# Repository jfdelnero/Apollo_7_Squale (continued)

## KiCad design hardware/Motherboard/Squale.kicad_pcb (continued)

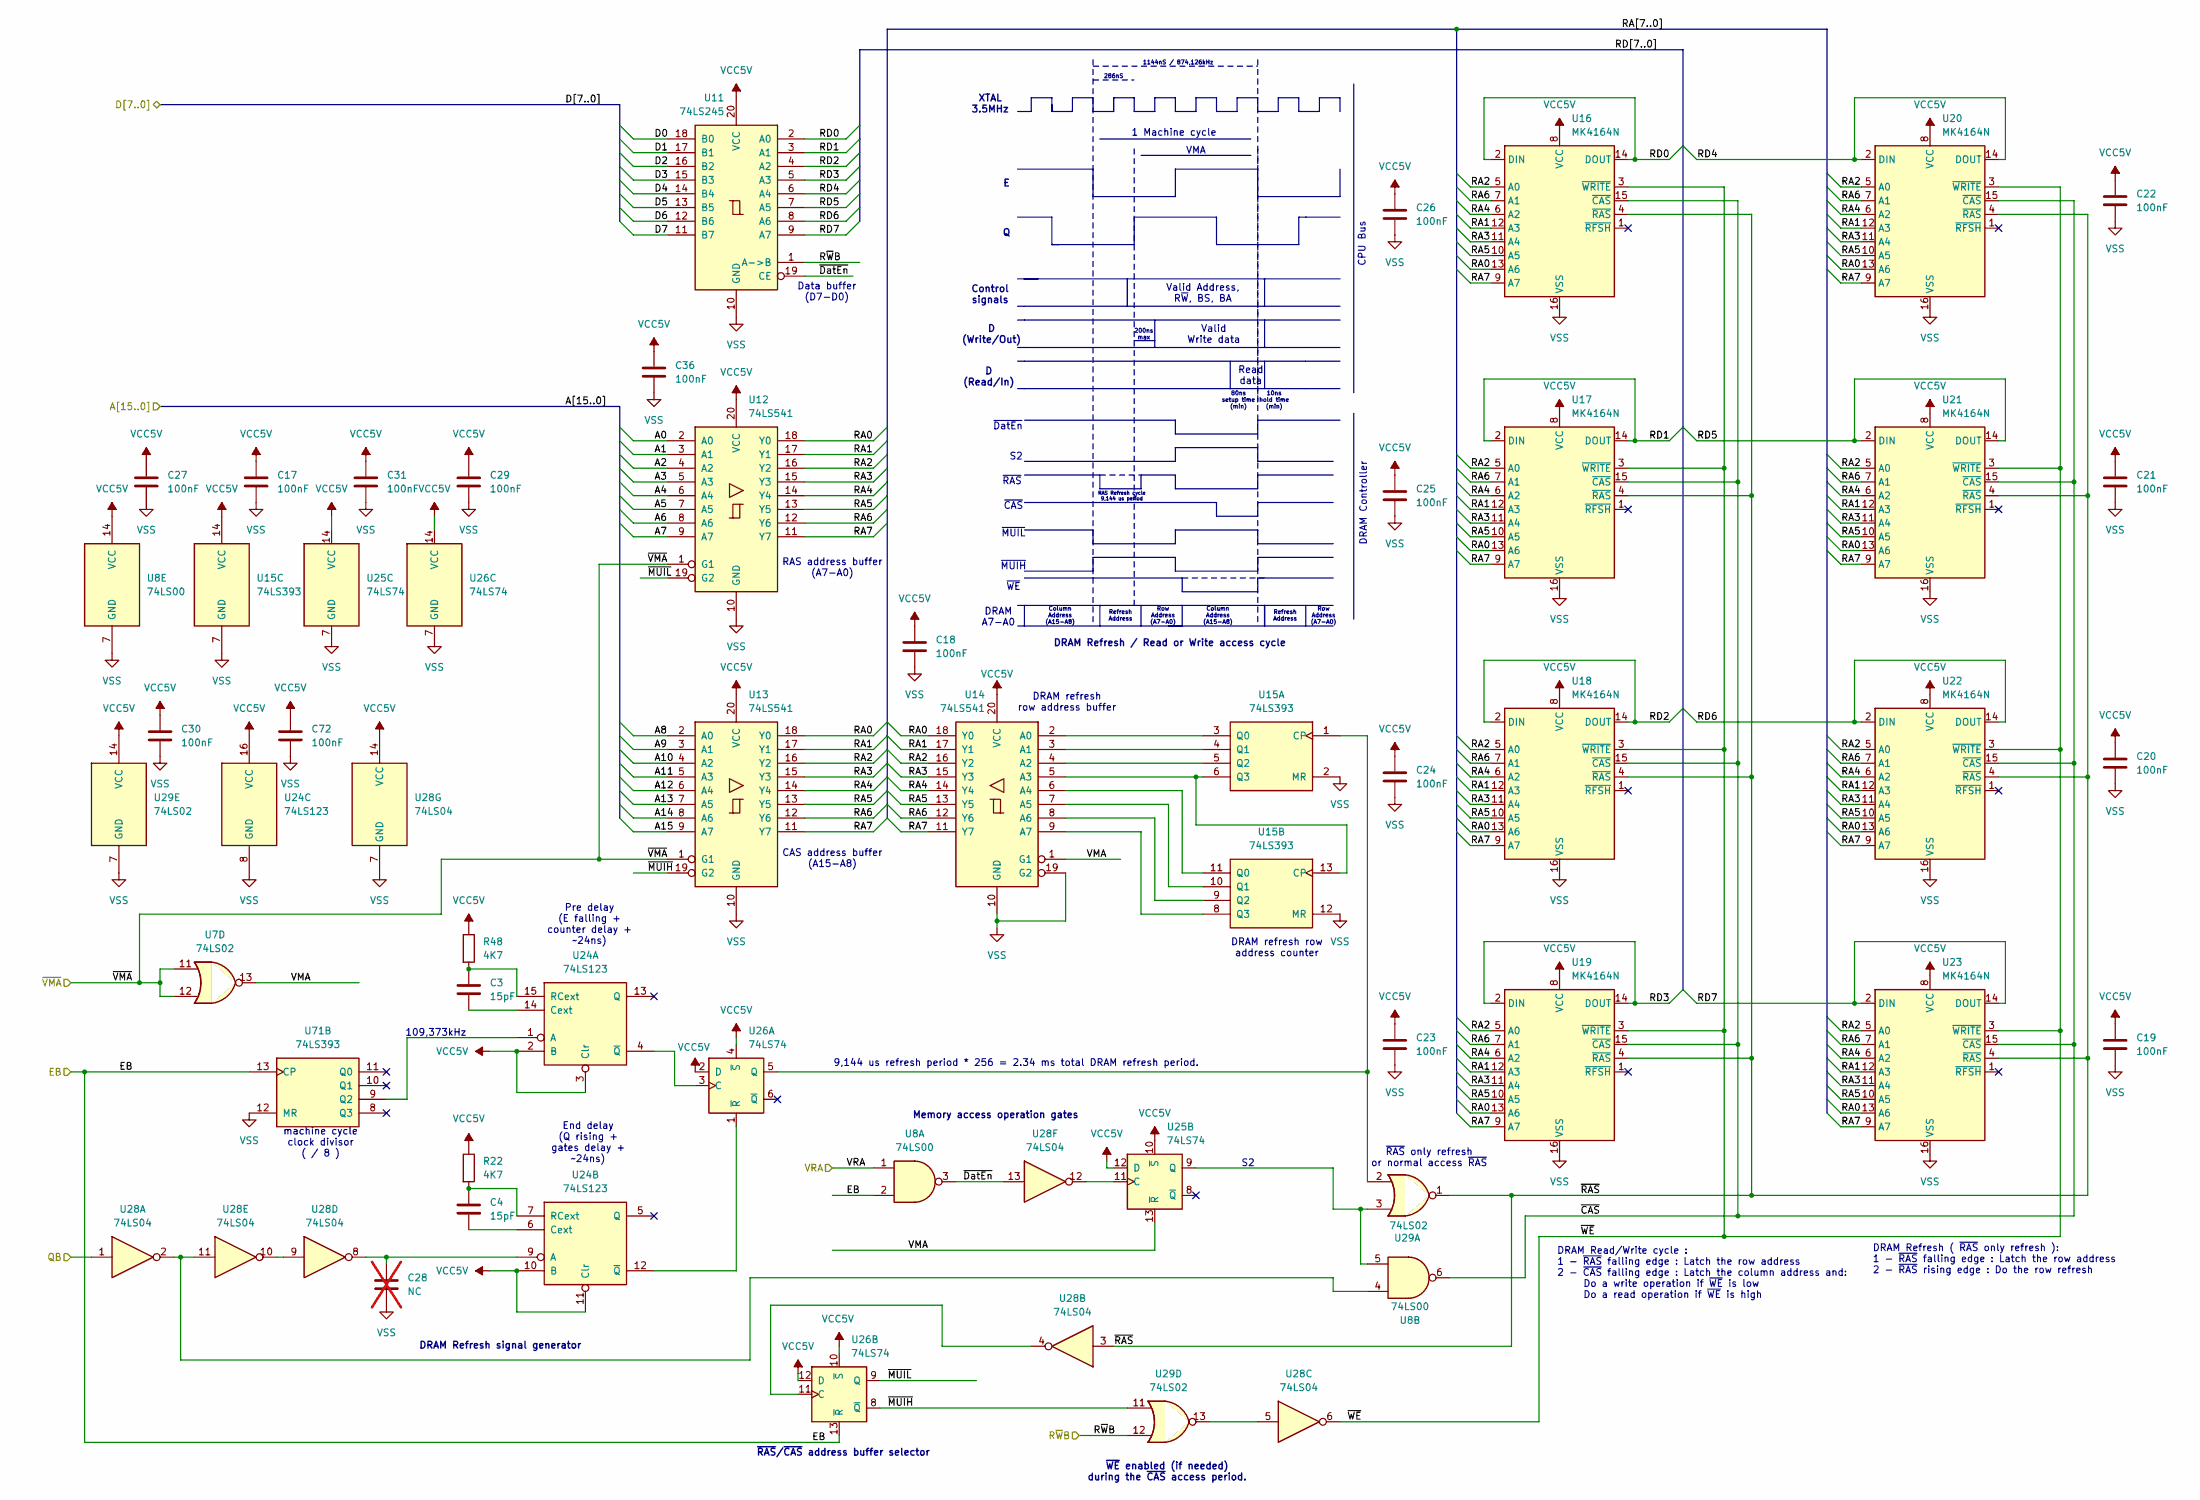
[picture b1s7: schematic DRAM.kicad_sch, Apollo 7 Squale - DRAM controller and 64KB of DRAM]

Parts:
C3, C4: 15pF; C_Disc_D3.0mm_W1.6mm_P2.50mm
C17, C18, C19, C20, C21, C22, C23, C24, C25, C26, C27, C29, C30, C31, C36, C72: 100nF; C_Disc_D9.0mm_W2.5mm_P5.00mm
C28: NC; C_Disc_D9.0mm_W2.5mm_P5.00mm; not fitted
R22, R48: 4K7; R_Axial_DIN0309_L9.0mm_D3.2mm_P12.70mm_Horizontal
U7, U29: 74LS02; DIP-14_W7.62mm_Socket
U8: 74LS00; DIP-14_W7.62mm_Socket
U11: 74LS245; DIP-20_W7.62mm_Socket
U12, U13, U14: 74LS541; DIP-20_W7.62mm_Socket
U15, U71: 74LS393; DIP-14_W7.62mm_Socket
U16, U17, U18, U19, U20, U21, U22, U23: MK4164N; DIP-16_W7.62mm_Socket
U24: 74LS123; DIP-16_W7.62mm_Socket
U25, U26: 74LS74; DIP-14_W7.62mm_Socket
U28: 74LS04; DIP-14_W7.62mm_Socket

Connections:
/A0: U12.2 (A0); also elsewhere on the board
/A1: U12.3 (A1); also elsewhere on the board
/A2: U12.4 (A2); also elsewhere on the board
/A3: U12.5 (A3); also elsewhere on the board
/A4: U12.6 (A4); also elsewhere on the board
/A5: U12.7 (A5); also elsewhere on the board
/A6: U12.8 (A6); also elsewhere on the board
/A7: U12.9 (A7); also elsewhere on the board
/A8: U13.2 (A0); also elsewhere on the board
/A9: U13.3 (A1); also elsewhere on the board
/A10: U13.4 (A2); also elsewhere on the board
/A11: U13.5 (A3); also elsewhere on the board
/A12: U13.6 (A4); also elsewhere on the board
/A13: U13.7 (A5); also elsewhere on the board
/A14: U13.8 (A6); also elsewhere on the board
/A15: U13.9 (A7); also elsewhere on the board
/CPU/EB: U8.2, U26.13 (~R), U71.13 (CP); also elsewhere on the board
/CPU/QB: U28.1; also elsewhere on the board
/CPU/R~WB: U11.1 (A->B), U29.12; also elsewhere on the board
/CPU/VRA: U8.1; also elsewhere on the board
/CPU/~VMA: U7.11, U7.12, U12.1 (G1), U13.1 (G1); also elsewhere on the board
/D0: U11.18 (B0); also elsewhere on the board
/D1: U11.17 (B1); also elsewhere on the board
/D2: U11.16 (B2); also elsewhere on the board
/D3: U11.15 (B3); also elsewhere on the board
/D4: U11.14 (B4); also elsewhere on the board
/D5: U11.13 (B5); also elsewhere on the board
/D6: U11.12 (B6); also elsewhere on the board
/D7: U11.11 (B7); also elsewhere on the board
/DRAM/RA0: U12.18 (Y0), U13.18 (Y0), U14.18 (Y0), U16.13 (A6), U17.13 (A6), U18.13 (A6), U19.13 (A6), U20.13 (A6), U21.13 (A6), U22.13 (A6), U23.13 (A6)
/DRAM/RA1: U12.17 (Y1), U13.17 (Y1), U14.17 (Y1), U16.12 (A3), U17.12 (A3), U18.12 (A3), U19.12 (A3), U20.12 (A3), U21.12 (A3), U22.12 (A3), U23.12 (A3)
/DRAM/RA2: U12.16 (Y2), U13.16 (Y2), U14.16 (Y2), U16.5 (A0), U17.5 (A0), U18.5 (A0), U19.5 (A0), U20.5 (A0), U21.5 (A0), U22.5 (A0), U23.5 (A0)
/DRAM/RA3: U12.15 (Y3), U13.15 (Y3), U14.15 (Y3), U16.11 (A4), U17.11 (A4), U18.11 (A4), U19.11 (A4), U20.11 (A4), U21.11 (A4), U22.11 (A4), U23.11 (A4)
/DRAM/RA4: U12.14 (Y4), U13.14 (Y4), U14.14 (Y4), U16.6 (A2), U17.6 (A2), U18.6 (A2), U19.6 (A2), U20.6 (A2), U21.6 (A2), U22.6 (A2), U23.6 (A2)
/DRAM/RA5: U12.13 (Y5), U13.13 (Y5), U14.13 (Y5), U16.10 (A5), U17.10 (A5), U18.10 (A5), U19.10 (A5), U20.10 (A5), U21.10 (A5), U22.10 (A5), U23.10 (A5)
/DRAM/RA6: U12.12 (Y6), U13.12 (Y6), U14.12 (Y6), U16.7 (A1), U17.7 (A1), U18.7 (A1), U19.7 (A1), U20.7 (A1), U21.7 (A1), U22.7 (A1), U23.7 (A1)
/DRAM/RA7: U12.11 (Y7), U13.11 (Y7), U14.11 (Y7), U16.9 (A7), U17.9 (A7), U18.9 (A7), U19.9 (A7), U20.9 (A7), U21.9 (A7), U22.9 (A7), U23.9 (A7)
/DRAM/RD0: U11.2 (A0), U16.2 (DIN), U16.14 (DOUT)
/DRAM/RD1: U11.3 (A1), U17.2 (DIN), U17.14 (DOUT)
/DRAM/RD2: U11.4 (A2), U18.2 (DIN), U18.14 (DOUT)
/DRAM/RD3: U11.5 (A3), U19.2 (DIN), U19.14 (DOUT)
/DRAM/RD4: U11.6 (A4), U20.2 (DIN), U20.14 (DOUT)
/DRAM/RD5: U11.7 (A5), U21.2 (DIN), U21.14 (DOUT)
/DRAM/RD6: U11.8 (A6), U22.2 (DIN), U22.14 (DOUT)
/DRAM/RD7: U11.9 (A7), U23.2 (DIN), U23.14 (DOUT)
/DRAM/VMA: U7.13, U14.1 (G1), U25.13 (~R)
/DRAM/~CAS: U8.6, U16.15 (~CAS), U17.15 (~CAS), U18.15 (~CAS), U19.15 (~CAS), U20.15 (~CAS), U21.15 (~CAS), U22.15 (~CAS), U23.15 (~CAS)
/DRAM/~DatEn: U8.3, U11.19 (CE), U28.13
/DRAM/~MUIH: U13.19 (G2), U26.8 (~Q), U29.11
/DRAM/~MUIL: U12.19 (G2), U26.9 (Q)
/DRAM/~RAS: U16.4 (~RAS), U17.4 (~RAS), U18.4 (~RAS), U19.4 (~RAS), U20.4 (~RAS), U21.4 (~RAS), U22.4 (~RAS), U23.4 (~RAS), U28.3, U29.1
/DRAM/~WE: U16.3 (~WRITE), U17.3 (~WRITE), U18.3 (~WRITE), U19.3 (~WRITE), U20.3 (~WRITE), U21.3 (~WRITE), U22.3 (~WRITE), U23.3 (~WRITE), U28.6
unnamed: U14.2 (A0), U15.3 (Q0)
unnamed: U14.3 (A1), U15.4 (Q1)
unnamed: U14.4 (A2), U15.5 (Q2)
unnamed: U14.5 (A3), U15.6 (Q3), U15.13 (CP)
unnamed: U14.6 (A4), U15.11 (Q0)
unnamed: U14.7 (A5), U15.10 (Q1)
unnamed: U14.8 (A6), U15.9 (Q2)
unnamed: U14.9 (A7), U15.8 (Q3)
unnamed: U15.1 (CP), U26.5 (Q), U29.2
unnamed: U24.1 (A), U71.9 (Q2)
unnamed: C3.2, U24.14 (Cext)
unnamed: C3.1, R48.2, U24.15 (RCext)
unnamed: U24.4 (~Q), U26.3 (C)
unnamed: C28.1, U24.9 (A), U28.8
unnamed: C4.2, U24.6 (Cext)
unnamed: C4.1, R22.2, U24.7 (RCext)
unnamed: U24.12 (~Q), U26.1 (~R)
unnamed: U25.11 (C), U28.12
unnamed: U8.5, U25.9 (Q), U29.3
unnamed: U26.11 (C), U28.4
unnamed: U28.5, U29.13
unnamed: U28.9, U28.10
unnamed: U8.4, U28.2, U28.11
VCC5V: C17.1, C18.1, C19.1, C20.1, C21.1, C22.1, C23.1, C24.1, C25.1, C26.1, C27.1, C29.1, C30.1, C31.1, C36.1, C72.1, R22.1, R48.1, U8.14 (VCC), U11.20 (VCC), U12.20 (VCC), U13.20 (VCC), U14.20 (VCC), U15.14 (VCC), U16.8 (VCC), U17.8 (VCC), U18.8 (VCC), U19.8 (VCC), U20.8 (VCC), U21.8 (VCC), U22.8 (VCC), U23.8 (VCC), U24.2 (B), U24.3 (Clr), U24.10 (B), U24.11 (Clr), U24.16 (VCC), U25.10 (~S), U25.12 (D), U25.14 (VCC), U26.2 (D), U26.4 (~S), U26.10 (~S), U26.12 (D), U26.14 (VCC), U28.14 (VCC), U29.14 (VCC); also elsewhere on the board
VSS: C17.2, C18.2, C19.2, C20.2, C21.2, C22.2, C23.2, C24.2, C25.2, C26.2, C27.2, C28.2, C29.2, C30.2, C31.2, C36.2, C72.2, U8.7 (GND), U11.10 (GND), U12.10 (GND), U13.10 (GND), U14.10 (GND), U14.19 (G2), U15.2 (MR), U15.7 (GND), U15.12 (MR), U16.16 (VSS), U17.16 (VSS), U18.16 (VSS), U19.16 (VSS), U20.16 (VSS), U21.16 (VSS), U22.16 (VSS), U23.16 (VSS), U24.8 (GND), U25.7 (GND), U26.7 (GND), U28.7 (GND), U29.7 (GND), U71.12 (MR); also elsewhere on the board

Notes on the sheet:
CPU Bus
~{WE}
Control signals
Read data
DRAM refresh row address buffer
RAS address buffer (A7-A0)
Memory access operation gates
~{RAS} only refresh or normal access ~{RAS}
Column Address (A15-A8)
Valid Write data
109,373kHz
~{RAS}
CAS address buffer (A15-A8)
XTAL 3.5MHz
Row Address (A7-A0)
286nS
machine cycle clock divisor ( / 8 )
Valid Address, R~{W}, BS, BA
DRAM Controller
DRAM refresh row address counter
D (Read/In)
D (Write/Out)
~{WE} enabled (if needed) during the ~{CAS} access period.
~{MUIH}
End delay (Q rising + gates delay + ~24ns)
~{MUIL}
200ns max
~{DatEn}
DRAM A7-A0
Refresh Address
9,144 us refresh period * 256 = 2.34 ms total DRAM refresh period.
10ns hold time (min)
VMA
DRAM Refresh signal generator
DRAM Refresh ( ~{RAS} only refresh ): 1 - ~{RAS} falling edge : Latch the row address 2 - ~{RAS} rising edge : Do the row refresh
~{RAS}/~{CAS} address buffer selector
1 Machine cycle
Data buffer (D7-D0)
80ns setup time (min)
DRAM Refresh / Read or Write access cycle

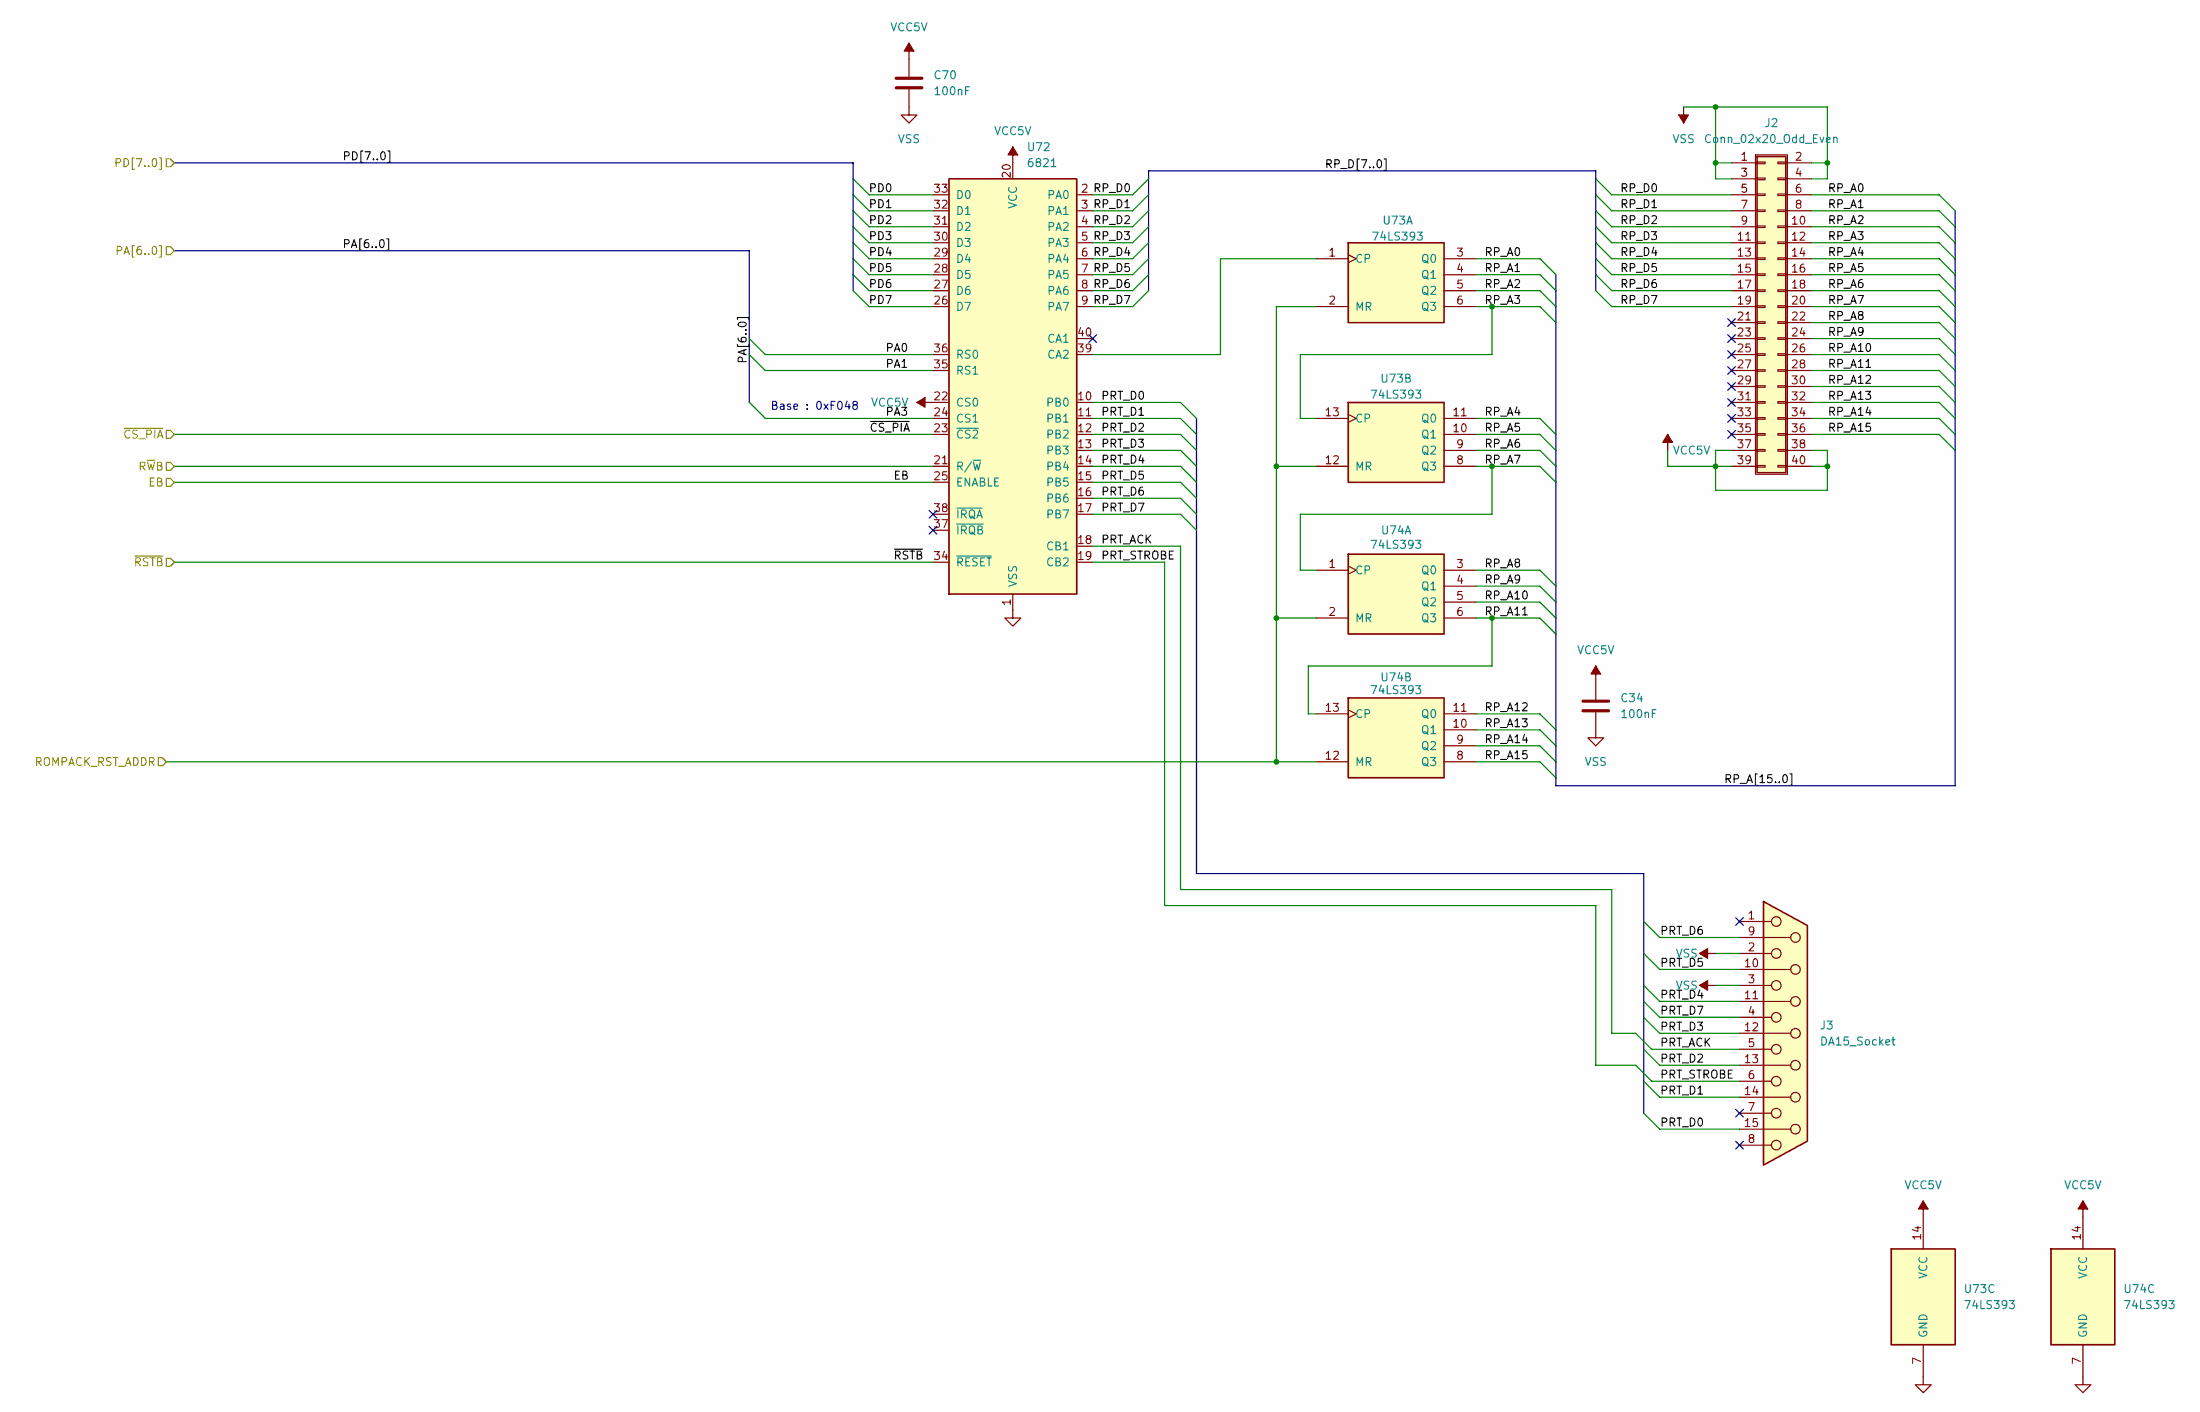
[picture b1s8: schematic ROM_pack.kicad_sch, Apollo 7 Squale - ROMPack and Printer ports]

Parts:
C34, C70: 100nF; C_Disc_D9.0mm_W2.5mm_P5.00mm
J2: Conn_02x20_Odd_Even; Ribbon_Conn
J3: DA15_Socket; DSUB-15_Pins_Horizontal_P2.77x2.84mm_EdgePinOffset9.40mm
U72: 6821; DIP-40_W15.24mm_Socket
U73, U74: 74LS393; DIP-14_W7.62mm_Socket

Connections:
/CPU/EB: U72.25 (ENABLE); also elsewhere on the board
/CPU/R~WB: U72.21 (R/~W); also elsewhere on the board
/CPU/~CS_PIA: U72.23 (~CS2); also elsewhere on the board
/Keyboard/ROMPACK_RST_ADDR: U73.2 (MR), U73.12 (MR), U74.2 (MR), U74.12 (MR); also elsewhere on the board
/Keyboard/~RSTB: U72.34 (~RESET); also elsewhere on the board
/PA0: U72.36 (RS0); also elsewhere on the board
/PA1: U72.35 (RS1); also elsewhere on the board
/PA3: U72.24 (CS1); also elsewhere on the board
/PD0: U72.33 (D0); also elsewhere on the board
/PD1: U72.32 (D1); also elsewhere on the board
/PD2: U72.31 (D2); also elsewhere on the board
/PD3: U72.30 (D3); also elsewhere on the board
/PD4: U72.29 (D4); also elsewhere on the board
/PD5: U72.28 (D5); also elsewhere on the board
/PD6: U72.27 (D6); also elsewhere on the board
/PD7: U72.26 (D7); also elsewhere on the board
/ROM_pack/PRT_ACK: J3.5, U72.18 (CB1)
/ROM_pack/PRT_D0: J3.15, U72.10 (PB0)
/ROM_pack/PRT_D1: J3.14, U72.11 (PB1)
/ROM_pack/PRT_D2: J3.13, U72.12 (PB2)
/ROM_pack/PRT_D3: J3.12, U72.13 (PB3)
/ROM_pack/PRT_D4: J3.11 (P111), U72.14 (PB4)
/ROM_pack/PRT_D5: J3.10, U72.15 (PB5)
/ROM_pack/PRT_D6: J3.9, U72.16 (PB6)
/ROM_pack/PRT_D7: J3.4, U72.17 (PB7)
/ROM_pack/PRT_STROBE: J3.6, U72.19 (CB2)
/ROM_pack/RP_A0: J2.6, U73.3 (Q0)
/ROM_pack/RP_A1: J2.8, U73.4 (Q1)
/ROM_pack/RP_A2: J2.10, U73.5 (Q2)
/ROM_pack/RP_A3: J2.12, U73.6 (Q3), U73.13 (CP)
/ROM_pack/RP_A4: J2.14, U73.11 (Q0)
/ROM_pack/RP_A5: J2.16, U73.10 (Q1)
/ROM_pack/RP_A6: J2.18, U73.9 (Q2)
/ROM_pack/RP_A7: J2.20, U73.8 (Q3), U74.1 (CP)
/ROM_pack/RP_A8: J2.22, U74.3 (Q0)
/ROM_pack/RP_A9: J2.24, U74.4 (Q1)
/ROM_pack/RP_A10: J2.26, U74.5 (Q2)
/ROM_pack/RP_A11: J2.28, U74.6 (Q3), U74.13 (CP)
/ROM_pack/RP_A12: J2.30, U74.11 (Q0)
/ROM_pack/RP_A13: J2.32, U74.10 (Q1)
/ROM_pack/RP_A14: J2.34, U74.9 (Q2)
/ROM_pack/RP_A15: J2.36, U74.8 (Q3)
/ROM_pack/RP_D0: J2.5, U72.2 (PA0)
/ROM_pack/RP_D1: J2.7, U72.3 (PA1)
/ROM_pack/RP_D2: J2.9, U72.4 (PA2)
/ROM_pack/RP_D3: J2.11, U72.5 (PA3)
/ROM_pack/RP_D4: J2.13, U72.6 (PA4)
/ROM_pack/RP_D5: J2.15, U72.7 (PA5)
/ROM_pack/RP_D6: J2.17, U72.8 (PA6)
/ROM_pack/RP_D7: J2.19, U72.9 (PA7)
unnamed: U72.39 (CA2), U73.1 (CP)
VCC5V: C34.1, C70.1, J2.37, J2.38, J2.39, J2.40, U72.20 (VCC), U72.22 (CS0), U73.14 (VCC), U74.14 (VCC); also elsewhere on the board
VSS: C34.2, C70.2, J2.1, J2.2, J2.3, J2.4, J3.2, J3.3, U72.1 (VSS), U73.7 (GND), U74.7 (GND); also elsewhere on the board

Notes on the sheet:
Base : 0xF048

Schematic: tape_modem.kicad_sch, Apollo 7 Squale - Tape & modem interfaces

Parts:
C5: 22pF; C_Disc_D3.0mm_W1.6mm_P2.50mm
C6: 10pF; C_Disc_D3.0mm_W1.6mm_P2.50mm
C7, C8: 10uF 50V; C_Radial_D6.3mm_H5.0mm_P2.50mm
C9, C11, C12, C13, C39, C40, C41: 100nF; C_Disc_D9.0mm_W2.5mm_P5.00mm
C10: 68pF; C_Disc_D6.0mm_W2.5mm_P5.00mm
D1, D2: 1N4148; D_DO-35_SOD27_P12.70mm_Horizontal
J5: DIN-5_180degree; DIN5-RA-PTH
J6: DE9_Socket; DSUB-9_Socket_Horizontal_P2.77x2.54mm_EdgePinOffset9.40mm
P1: VR10K; Potentiometer_Piher_PT-10-H01_Horizontal
R23, R26, R29, R30, R33, R34, R35, R37: 10K; R_Axial_DIN0309_L9.0mm_D3.2mm_P12.70mm_Horizontal
R24: 330K; R_Axial_DIN0309_L9.0mm_D3.2mm_P12.70mm_Horizontal
R25, R27, R36: 47K; R_Axial_DIN0309_L9.0mm_D3.2mm_P12.70mm_Horizontal
R28: 33K3; R_Axial_DIN0309_L9.0mm_D3.2mm_P12.70mm_Horizontal
R31, R47: 470R; R_Axial_DIN0309_L9.0mm_D3.2mm_P12.70mm_Horizontal
R32: 22K; R_Axial_DIN0309_L9.0mm_D3.2mm_P12.70mm_Horizontal
U67: TL084; DIP-14_W7.62mm_Socket
U68: EFB7510; DIP-18_W7.62mm_Socket
U69: MC6850; DIP-24_W15.24mm_Socket
U70: 74LS02; DIP-14_W7.62mm_Socket
U71: 74LS393; DIP-14_W7.62mm_Socket
Y2: 3.579MHz; Crystal_HC18-U_Vertical

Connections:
/CPU/EB: U69.14 (E); also elsewhere on the board
/CPU/R~WB: U69.13 (R/~W); also elsewhere on the board
/CPU/~CS_ACIA: U69.9 (CS2); also elsewhere on the board
/PA0: U69.11 (RS); also elsewhere on the board
/PD0: U69.22 (D0); also elsewhere on the board
/PD1: U69.21 (D1); also elsewhere on the board
/PD2: U69.20 (D2); also elsewhere on the board
/PD3: U69.19 (D3); also elsewhere on the board
/PD4: U69.18 (D4); also elsewhere on the board
/PD5: U69.17 (D5); also elsewhere on the board
/PD6: U69.16 (D6); also elsewhere on the board
/PD7: U69.15 (D7); also elsewhere on the board
/Sound/MODEM_RING: J6.2; also elsewhere on the board
/Tape-Modem/IN_1: J5.3, R35.1, R36.2, R37.2
/Tape-Modem/IN_2: J5.5, R35.2
/Tape-Modem/MDM_CLK_19K2: U68.16 (RxCLK), U69.3 (Rx_CLK), U70.3, U71.1 (CP)
/Tape-Modem/MDM_CLK_TX: U69.4 (Tx_CLK), U70.4
/Tape-Modem/OUT_1V_LEVEL: J5.4, R33.2, R34.1
/Tape-Modem/OUT_50mV_LEVEL: J5.1, R34.2, R47.2
/Tape-Modem/SYS_MDM_LINE: J6.1; also elsewhere on the board
/Tape-Modem/SYS_MDM_MC_~BC: U68.18 (MC/~BC), U70.8, U70.11, U70.12; also elsewhere on the board
unnamed: C9.1, R23.2
unnamed: C10.1, C11.2, R24.1, U67.8
unnamed: C12.1, R26.2
unnamed: C13.1, R32.1
unnamed: C11.1, C12.2, D1.2 (A), D2.1 (K), R25.1
unnamed: C9.2, C10.2, D1.1 (K), D2.2 (A), R24.2, U67.9 (-)
unnamed: R28.1, R29.2, R31.2, R33.1, U67.1
unnamed: R28.2, R32.2, U67.2 (-)
unnamed: J6.4, R31.1, U67.5 (+)
unnamed: R29.1, R30.2, R36.1, U67.6 (-)
unnamed: R26.1, R27.2, U67.13 (-)
unnamed: C13.2, U68.4 (ATO)
unnamed: R30.1, U67.7, U68.7 (RAI)
unnamed: R27.1, U67.14, U68.13 (RDI)
unnamed: R23.1, U68.5 (RFO)
unnamed: P1.2, U68.9 (RSA)
unnamed: U68.11 (RXD), U69.2 (Rx_Data)
unnamed: U68.17 (TXD), U69.6 (Tx_Data)
unnamed: P1.3, U68.10 (VREF)
unnamed: C5.1, U68.15 (XTAL_IN), Y2.1
unnamed: C6.2, U68.14 (XTAL_OUT), Y2.2
unnamed: U68.12 (~DCD), U69.23 (~DCD)
unnamed: U68.2 (~RTS), U69.5 (~RTS)
unnamed: U70.1, U70.6
unnamed: U70.5, U70.10
unnamed: U70.2, U70.13
unnamed: U70.9, U71.6 (Q3)
VCC5V: C8.1, C39.1, C40.1, J6.3, U67.4 (V+), U68.1 (V+), U69.8 (CS0), U69.10 (CS1), U69.12 (VCC), U70.14 (VCC), U71.14 (VCC); also elsewhere on the board
VEE5V: C7.1, C41.2, U67.11 (V-), U68.6 (V-); also elsewhere on the board
VSS: C5.2, C6.1, C7.2, C8.2, C39.2, C40.2, C41.1, J5.2, J6.5, J6.8, P1.1, R25.2, R37.1, R47.1, U67.3 (+), U67.10 (+), U67.12 (+), U68.3 (GNDD), U68.8 (GNDA), U69.1 (VSS), U69.24 (~CTS), U70.7 (GND), U71.2 (MR), U71.7 (GND); also elsewhere on the board

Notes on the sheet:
+/- 1.20V
Typical output level : +/- 1.56V
Peak limiter band pass filter
TX Clock source selector. SYS_MDM_MC_~{BC} Low : 1200 Hz (75 Baud) SYS_MDM_MC_~{BC} High : 19200 Hz (1200 Baud)
G = 47K/10K = 4,7 20 * log 4,7 = 13,44 dB
/ 22.28 -26.95 dB
High pass filter Cutoff frequency (-3 dB) : fc = 1 / ( 2 * PI * 10K * 100nF ) = 159.15 Hz
peak limiter (1V)
Peak limiter band pass filter curve
Duplexer
Low pass filter G = 330K/10K = 33 20 * log 33 = 30,37 dB Cutoff frequency (-3 dB) : fc = 1 / ( 2 * PI * 330K * 68pF ) = 7092.47 Hz
+/- 54mV
max level : +8 dBm (< 6 VPP)
(1200 Hz -> 75 Baud) (19200 Hz -> 1200 Baud)
G = 33K3/22K = * 1.514 20 * log 1.514 = +3,6 dB
+/- 2.36V
TX baudrate selection Low = 75 baud High = 1200 baud.
RxCLK divisor 19200Hz / 16 = 1200 Hz (1200 Hz -> 75 Baud)

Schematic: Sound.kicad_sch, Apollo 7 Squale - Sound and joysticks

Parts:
C14: ??; C_Disc_D9.0mm_W2.5mm_P5.00mm
C15: 10uF 50V; C_Radial_D6.3mm_H5.0mm_P2.50mm
C42: 100nF; C_Disc_D9.0mm_W2.5mm_P5.00mm
J7, J8: DE9_Pins; DSUB-9_Pins_Horizontal_P2.77x2.54mm_EdgePinOffset9.40mm
R38, R39: 1K; R_Axial_DIN0309_L9.0mm_D3.2mm_P12.70mm_Horizontal
R40: 10K; R_Axial_DIN0309_L9.0mm_D3.2mm_P12.70mm_Horizontal
U29: 74LS02; DIP-14_W7.62mm_Socket
U65: AY-3-8910A; DIP-40_W15.24mm_Socket

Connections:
/A0: U29.6; also elsewhere on the board
/CPU/R~WB: U29.8; also elsewhere on the board
/CPU/~CS_AY: U29.5, U29.9; also elsewhere on the board
/Clocks/CLK_1.75MHz: U65.22 (CLOCK); also elsewhere on the board
/Keyboard/KEYB_CTRL: U65.7 (IOB6); also elsewhere on the board
/Keyboard/KEYB_LOCK: U65.9 (IOB4); also elsewhere on the board
/Keyboard/KEYB_SHIFT: U65.8 (IOB5); also elsewhere on the board
/Keyboard/~RSTB: U65.23 (~RESET); also elsewhere on the board
/PD0: U65.37 (DA0); also elsewhere on the board
/PD1: U65.36 (DA1); also elsewhere on the board
/PD2: U65.35 (DA2); also elsewhere on the board
/PD3: U65.34 (DA3); also elsewhere on the board
/PD4: U65.33 (DA4); also elsewhere on the board
/PD5: U65.32 (DA5); also elsewhere on the board
/PD6: U65.31 (DA6); also elsewhere on the board
/PD7: U65.30 (DA7); also elsewhere on the board
/Sound/JOY1_DOWN: J7.2, U65.19 (IOA2)
/Sound/JOY1_FIRE: J7.6, U65.14 (IOA7)
/Sound/JOY1_LEFT: J7.3, U65.20 (IOA1)
/Sound/JOY1_RIGHT: J7.4, U65.21 (IOA0)
/Sound/JOY1_UP: J7.1, U65.18 (IOA3)
/Sound/JOY2_DOWN: J8.2, U65.11 (IOB2)
/Sound/JOY2_FIRE: J8.6, U65.6 (IOB7)
/Sound/JOY2_LEFT: J8.3, U65.12 (IOB1)
/Sound/JOY2_RIGHT: J8.4, U65.13 (IOB0)
/Sound/JOY2_UP: J8.1, U65.10 (IOB3)
/Sound/LIGHTPEN_SWITCH: U65.16 (IOA5); also elsewhere on the board
/Sound/MODEM_RING: U65.15 (IOA6); also elsewhere on the board
/Sound/SOUND_OUT: C14.1, R39.2, R40.1; also elsewhere on the board
unnamed: C15.2, R39.1
unnamed: C15.1, R38.1, U65.3 (A), U65.4 (B), U65.38 (C)
unnamed: U29.4, U65.29 (BC1)
unnamed: U29.10, U65.27 (BDIR)
VCC5V: C42.1, J7.7, J8.7, U65.25 (A8), U65.28 (BC2), U65.40 (VCC); also elsewhere on the board
VSS: C14.2, C42.2, J7.8, J8.8, R38.2, R40.2, U65.1 (VSS), U65.24 (~A9); also elsewhere on the board

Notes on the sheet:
Base address : 0xF060

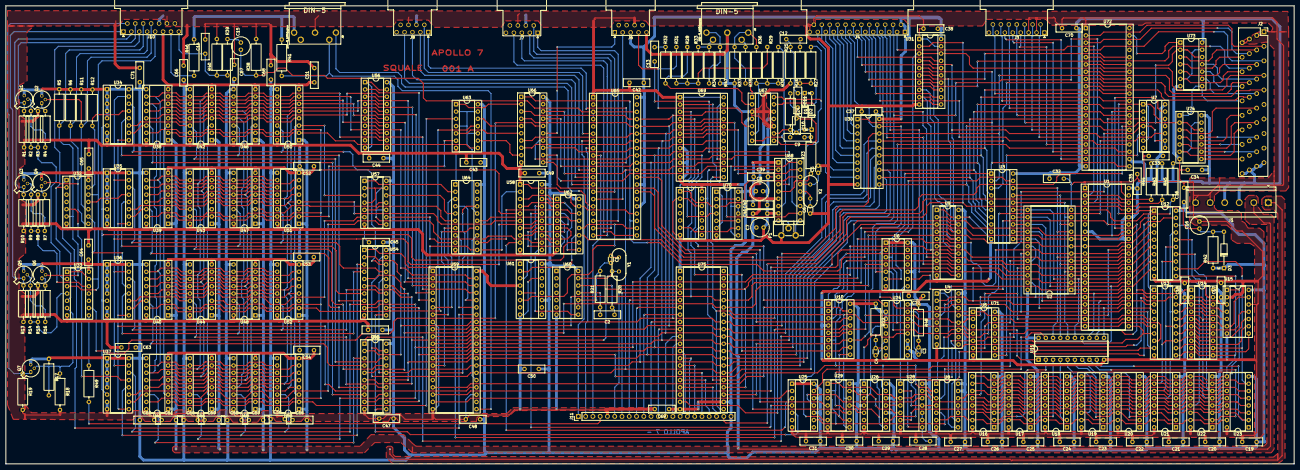
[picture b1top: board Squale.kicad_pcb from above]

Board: 2 copper layers, 450.0 x 160.0 mm, 219 parts (0 on the bottom side), 351 nets.

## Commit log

2019-10-14 Squale toolchain generation scripts.
2019-10-14 Squale Tape/Cartridge generators tools.
2019-10-14 linker script and program loader/header.
2019-10-14 gcc 4.6.3 cross compile patch.
2019-10-14 A very first/simple Squale Intro/demo.
2019-10-14 WIP : Squale 3D demo.
2019-10-15 Squale specific headers.
2019-10-17 Add more Squale HW definition.
2019-10-17 Update HW defines.
2019-10-17 Update HW defines. 3d objects change.
2019-10-19 Build tape wav file.
2019-10-19 use WR_BYTE instead of a pointer. fix some glitches on the real machine : wait the end of the last line draw.
2019-10-19 interrupt driven music player.
2019-10-20 YM player : YM data are now "packed". Bigger YM music can now be used.
2019-10-20 A "poor-man"/quick and dirty ym packer/converter. Anyway this "packed" form is now played on a the 6809 machine without the need to deflate the file.
2019-10-23 code speed optimization.
2019-10-23 Do not poll the ef9365 status registers anymore for the vblank.
2019-10-24 New function : display vectorized/rle packed sprite.
2019-10-27 moved.
2019-10-27 music build process changed.
2019-10-27 Fix build.
2019-10-27 WIP : Multi-parts demo triggers
2019-10-27 clear msb.
2019-10-27 makefile cleanup.
2019-10-27 new tool : bmp to rle packed image.
2019-10-27 demos bmp : some logos.
2019-10-27 Music : Warp 5 (Mad Max / Jochen Hippel)
2019-10-27 remove executable from the repository.
2019-10-27 a little fix.
2019-10-27 add footpage image.
2019-10-27 clear x,y msb
2019-10-27 revert the previous modification.
2019-10-27 Fix output image size.
2019-10-27 squale presentation screen.
2019-10-29 Presentation screen code moved.
2019-10-29 Squares screen.
2019-10-29 Startup logo screen.
2019-10-29 Segments screen.
2019-10-29 Jump screen.
2019-10-29 dots chaos screen.
2019-10-29 3D screen
2019-10-29 global defines.
2019-10-29 Remove unused variable.
2019-10-30 Use the WAIT_EF9365_READY macro to wait the EF9365.
2019-10-30 Optimizations to remove the flickering : better GPU usage : Do something with the CPU while the GPU is drawing the lines.
2019-10-30 Now working at 50 FPS ! :)
2019-10-30 Code optimizations : better GPU usage : Do something with the CPU while the GPU is drawing the lines.
2019-10-30 end screen credits added.
2019-10-30 demo parts position/duration modified.
2019-11-01 some pixels changes/fixes...
2019-11-01 bart.
2019-11-01 adding Bart.
2019-11-01 cleanup/ remove unused functions. Do something while the GPU is drawing the line.
2019-11-01 3D part is now auto selecting the next object.
2019-11-01 Bart added to the demo.
2019-11-01 some more pixels changes...
2019-11-01 some optimizations + unused functions removed.
2019-11-01 clear screen added.
2019-11-01 Don't wait for the vblank. TODO : add a delay after the vblank sync to suppress the 3d object flickering.
2019-11-01 unused objects removed.
2019-11-01 Rename the demo folder.
2019-11-01 typo.
2019-11-01 try to disable the gcc documentation in the build...
2019-11-01 clean : don't delete the include folder !
2019-11-02 disable boxes demo part.
2019-11-02 increase the rotation speed.
2019-11-02 vid_asm_func removed.
2019-11-02 Important changes in this effect : The 3 letters are moving/jumping independently of each others.
2019-11-02 vid_asm_func replaced.
2019-11-02 more minor fixes.
2019-11-02 Change a little bit the way the objects are rotating.
2019-11-02 Switch from 16 to 32 bytes YM page size : The final demo fit into the 32KB ROM with this new setting.
2019-11-02 String can be passed in parameter.
2019-11-02 version/date updated.
2019-11-02 Minor txt changes.
2019-11-02 new jumping texts.
2019-11-02 Change output name.
2019-11-02 floor position fix.
2019-11-02 Change date format.
2019-11-02 generate a 32KB ROM if possible.
2019-11-03 ROM and tape release output.
2019-11-03 not used anymore.
2019-11-03 better mrproper.
2019-11-03 mrproper.
2019-11-03 Squale intro binaries.
2019-11-07 squale & demo pictures.
2019-11-07 readme file.
2019-11-07 fix links.
2019-11-07 remove tabulation.
2019-11-07 fix header
2019-11-07 remove first separator.
2019-11-07 carriage return.
2019-11-07 news letter link.
2019-11-10 Ports/Connectors pinout.
2025-06-14 Fix ifl_head multiple definitions build error.
2025-08-14 Squale schematic : Initial commit. Work in progress ...
2025-08-21 PCBAnnot motherboard project.
2025-08-21 net rename + fix
2025-08-21 WIP.
2025-08-31 WIP -rom pack
2025-09-01 S30 bus + annotations fixes.
2025-09-02 wip : modem
2025-09-08 wip: tape / modem interface.
2025-09-09 LTspice modem filter simulation.
2025-09-09 R32 and R36 values fixed. Gain fixed.
2025-09-10 signals levels.
2025-09-11 cosmetic
2025-09-16 WIP : passives parts, cosmetic stuffs.
2025-09-16 duplicated U8E
2025-09-27 Footprints.
2025-09-27 net list
2025-09-27 first import.
2025-09-27 first ICs approximate placement
2025-09-28 Full & scripted placement, based on the PCBAnnot data.
2025-09-28 Fix DRAM address bus connection.
2025-10-02 Fix DRAM address bits ordering.
2025-10-02 missing addresses?
2025-10-04 Fix buffer direction
2025-10-04 fix dram address bit order.
2025-10-04 Fix vr connections.
2025-10-04 Some connections fixed.
2025-10-04 Net fixes.
2025-10-04 WIP : Motherboard layout.
2025-10-05 power traces wip..
2025-10-05 eprom vcc fix.
2025-10-06 fix footprint.
2025-10-06 fix footprint
2025-10-06 some footprints fixes and minor changes.
2025-10-06 Connectors footprint.
2025-10-06 Fix footprints and many drc errors.
2025-10-06 more fixes !
2025-10-07 connection fix + power line width.
2025-10-10 add some descriptions / comments.
2025-10-11 connection fix
2025-10-11 fixes
2025-10-11 github url + version
2025-10-12 Hello world !
2025-10-15 bouncing hello world.
2025-10-15 sound added.
2025-10-17 readme.
2025-10-17 3d preview
2025-10-18 fix ay sound function.
2025-10-18 ay sound generator : use a table.
2025-10-19 Manuel du Squale.
2025-10-19 fix tabs.
2025-10-19 fix.
2025-10-19 return fix.
2025-10-19 list fix
2025-10-19 return
2025-12-08 SS30 Floppy Disk Controller schematic : initial commit
2025-12-08 WIP : schematic
2025-12-08 board pictures
2025-12-08 WIP : annotation.
2025-12-14 fix some missing values.
2025-12-14 comment/notes added.
2025-12-14 port -> register
2025-12-20 Squale Monitor ROM dumper.
2025-12-21 cartridge dumper.
2025-12-22 squale cart dump demodulator.
2025-12-22 makefile clean up.
2026-01-01 Mosaic test program
